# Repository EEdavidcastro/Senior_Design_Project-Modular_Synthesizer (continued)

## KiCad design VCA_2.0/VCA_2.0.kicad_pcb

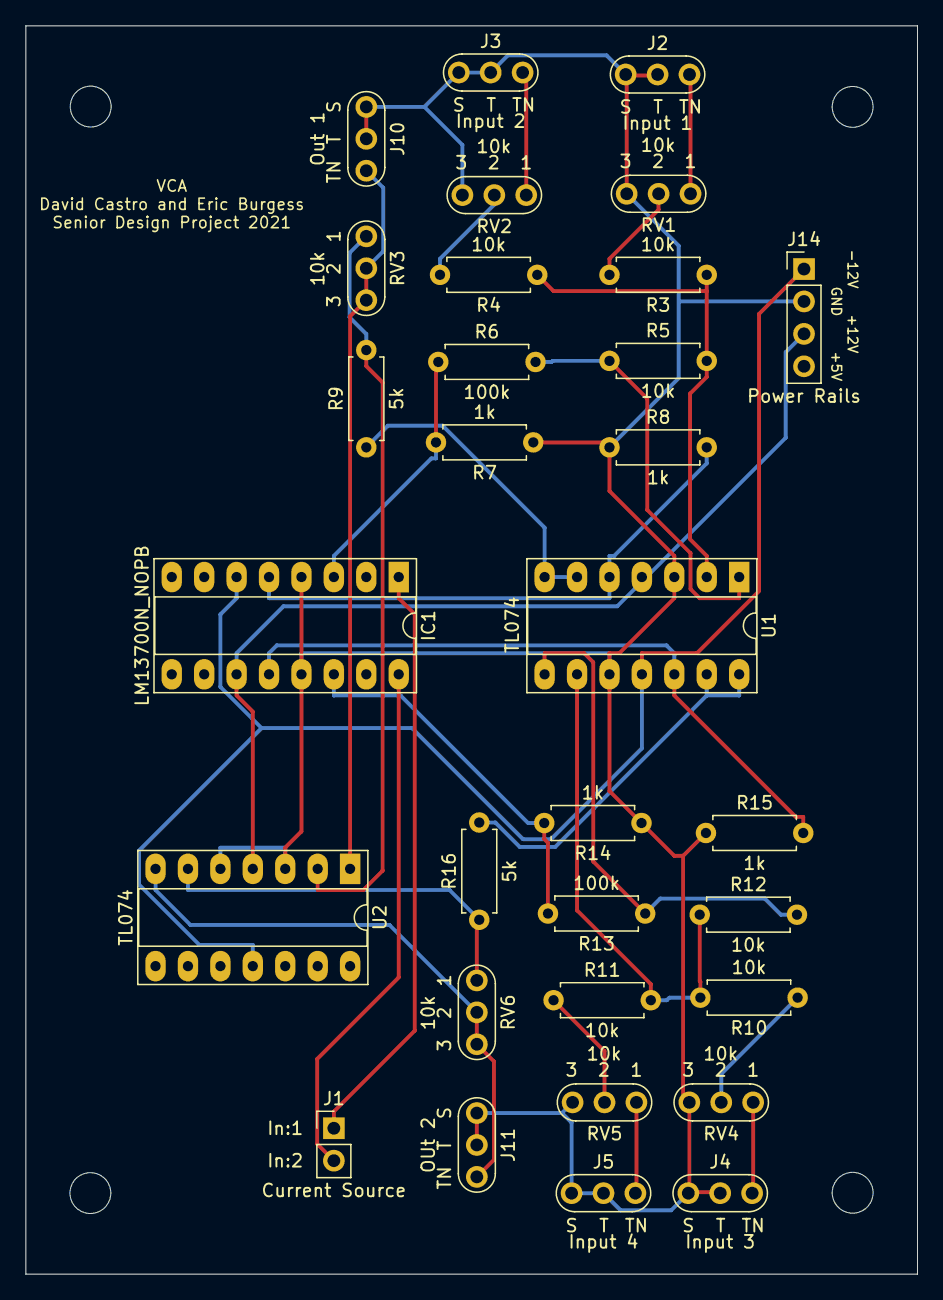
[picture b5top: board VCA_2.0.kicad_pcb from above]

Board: 2 copper layers, 69.9 x 97.8 mm, 31 parts (0 on the bottom side), 27 nets.

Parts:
IC1: LM13700N_NOPB; DIP-16_W7.62mm_Socket_LongPads
J1: Current Source; PinHeader_1x02_P2.54mm_Vertical
J2: Input 1; THONK-AudioJack-PJ398SM-W3.5mm
J3: Input 2; THONK-AudioJack-PJ398SM-W3.5mm
J4: Input 3; THONK-AudioJack-PJ398SM-W3.5mm
J5: Input 4; THONK-AudioJack-PJ398SM-W3.5mm
J10: Out 1; THONK-AudioJack-PJ398SM-W3.5mm
J11: OUt 2; THONK-AudioJack-PJ398SM-W3.5mm
J14: Power Rails; PinHeader_1x04_P2.54mm_Vertical
R3, R4, R5, R10, R11, R12: 10k; R_Axial_DIN0207_L6.3mm_D2.5mm_P7.62mm_Horizontal
R6, R13: 100k; R_Axial_DIN0207_L6.3mm_D2.5mm_P7.62mm_Horizontal
R7, R8, R14, R15: 1k; R_Axial_DIN0207_L6.3mm_D2.5mm_P7.62mm_Horizontal
R9, R16: 5k; R_Axial_DIN0207_L6.3mm_D2.5mm_P7.62mm_Horizontal
RV1, RV2, RV3, RV4, RV5, RV6: 10k; POT_3_THT
U1, U2: TL074; DIP-14_W7.62mm_Socket_LongPads

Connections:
+12V: IC1.11, J14.3, U1.4, U2.4
-12V: IC1.6, J14.1, U1.11, U2.11
GND: IC1.4, IC1.13, J2.S, J2.T, J3.S, J3.T, J4.S, J4.T, J5.S, J5.T, J10.S, J10.T, J11.S, J11.T, J14.2, R7.1, R8.1, R14.1, R15.1, RV1.3, RV2.3, RV4.3, RV5.3, U1.3, U1.10, U2.3, U2.5
unnamed: IC1.1, J1.1
unnamed: IC1.3, R6.1, R7.2
unnamed: IC1.5, R8.2, U1.5
unnamed: IC1.12, R15.2, U1.12
unnamed: IC1.14, R13.2, R14.2
unnamed: IC1.16, J1.2
unnamed: J2.TN, RV1.1
unnamed: J3.TN, RV2.1
unnamed: J4.TN, RV4.1
unnamed: J5.TN, RV5.1
unnamed: J10.TN, RV3.2, RV3.3, U2.1
unnamed: J11.TN, RV6.2, RV6.3, U2.7
unnamed: R3.1, R4.1, R5.2, U1.2
unnamed: R3.2, RV1.2
unnamed: R4.2, RV2.2
unnamed: R5.1, R6.2, U1.1
unnamed: R9.1, U1.6, U1.7
unnamed: R9.2, RV3.1, U2.2
unnamed: R10.1, RV4.2
unnamed: R10.2, R11.2, R12.1, U1.9
unnamed: R11.1, RV5.2
unnamed: R12.2, R13.1, U1.8
unnamed: R16.1, RV6.1, U2.6
unnamed: R16.2, U1.13, U1.14

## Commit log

2021-12-09 initial upload
